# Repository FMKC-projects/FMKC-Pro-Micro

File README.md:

# FMKC Pro Micro
The FMKC Pro Micro is a fork of the Goldfish type-C pro micro Rev C. The reason why this is forked is that at the time of writing, type-C Pro Micros are either A) really expensive, or B) ugly looking. This fork is planned to be a community-themes pro micro and hence also openly shared. We'll try to include everything so that you could make your own PCBWay (or similar) or order.

## Risks
At the time of writing, we haven't yet done a order of this fork. Despite when this run has been done and the files are "ready", you are still using this at your own risk.

## Repo Contents
**/cad** - KiCad source files.  
**/doc** - Schematics
**/bom** - The BOM-file as .xslx (or some other format)

## License Information
Released under the Creative Commons Attribution Share-Alike 4.0 License.  
https://creativecommons.org/licenses/by-sa/4.0/  

Original Arduino Mini Design by Team Arduino.  
Arduino Pro Mini Design by Spark Fun Electronics.  
Pro Micro Design by Spark Fun Electronics.  
Goldfish Design by Dr Derivative.  

## Related Projects
* [Alvaro](https://github.com/Ariamelon/Alvaro) by Ariamelon - A modified goldfish using 0603 components instead of 0402
* [Comet](https://github.com/vattern/comet) by Tokas - A modified goldfish using a different USB-C connector
* [Goldfish-clone-JLCPCB](https://github.com/JeremyJStarcher/Goldfish-clone-JLCPCB) by Jeremy J Starcher - A modified goldfish designed to meet JLCPCB's assembly requirements
* Elite-C from keeb.io - An unrelated and closed source project with similar design goals

## Potential vendors
* Potential single units available after production by [olli.works](https://olli.works)

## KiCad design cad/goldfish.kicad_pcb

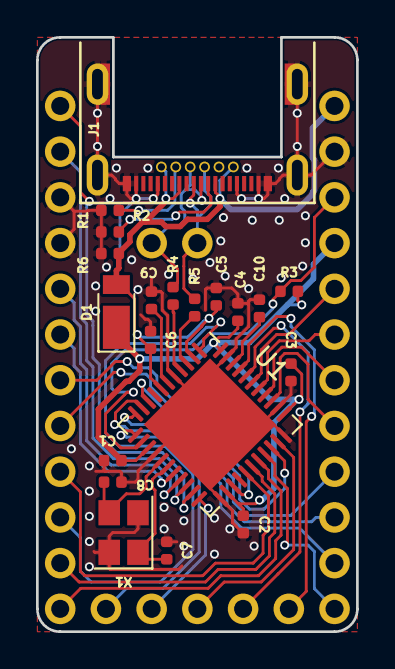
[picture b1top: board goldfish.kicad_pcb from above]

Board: 2 copper layers, 17.8 x 33.0 mm, 24 parts (0 on the bottom side), 37 nets.

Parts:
C1, C2, C3, C4, C5, C10: 0u1; C_0402_1005Metric
C6: 4u7; C_0402_1005Metric
C7, C8: 22p; C_0402_1005Metric
C9: 1u; C_0402_1005Metric
D1: D_Schottky; D_PowerDI-123
J1: USB-C; CX70M-24P1
J2: 01x02; Pins2
J3, J4: 01x12; Pins12
J5: 01x05; Pins5
R1, R2: 5k1; R_0402_1005Metric
R3, R6: 10k; R_0402_1005Metric
R4, R5: 22; R_0402_1005Metric
U1: ATmega32U4; QFN-44-1EP_7x7mm_P0.5mm_EP5.2x5.2mm_FORK
X1: 16MHz; Crystal_SMD_SeikoEpson_FA238-4Pin_3.2x2.5mm

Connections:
/D+: J1.A6, J1.B6, J2.1, R4.2
/D-: J1.A7, J1.B7, J2.2, R5.2
/PB1: J3.9, U1.9
/PB2: J3.11, U1.10
/PB3: J3.10, U1.11
/PB4: J4.2, U1.28
/PB5: J4.1, U1.29
/PB6: J3.12, U1.30
/PB7: J5.5, U1.12
/PC6: J4.5, U1.31
/PC7: J5.3, U1.32
/PD0: J4.7, U1.18
/PD1: J4.8, U1.19
/PD2: J4.11, U1.20
/PD3: J4.12, U1.21
/PD4: J4.6, U1.25
/PD5: J5.4, U1.22
/PD7: J4.4, U1.27
/PE6: J4.3, U1.1
/PF0: J5.1, U1.41
/PF1: J5.2, U1.40
/PF4: J3.5, U1.39
/PF5: J3.6, U1.38
/PF6: J3.7, U1.37
/PF7: J3.8, U1.36
/RESET: J3.3, R3.1, U1.13
GND: C1.2, C2.2, C3.2, C4.2, C5.2, C6.2, C7.2, C8.2, C9.2, C10.2, J1.A1, J1.A12, J1.B1, J1.B12, J1.S1, J3.2, J4.9, J4.10, R1.1, R2.1, R6.1, U1.5, U1.15, U1.23, U1.33, U1.35, U1.43, U1.45, X1.2, X1.4
unnamed: C7.1, U1.17, X1.1
unnamed: C8.1, U1.16, X1.3
unnamed: C9.1, U1.6
unnamed: C10.1, U1.42
unnamed: J1.A5, R1.2
unnamed: J1.B5, R2.2
unnamed: R4.1, U1.4
unnamed: R5.1, U1.3
VBUS: C5.1, C6.1, D1.2, J1.A4, J1.A9, J1.B4, J1.B9, J3.1, R6.2, U1.2, U1.7
VCC: C1.1, C2.1, C3.1, C4.1, D1.1, J3.4, R3.2, U1.14, U1.24, U1.34, U1.44

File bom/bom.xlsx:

Item # | *Ref Des | *Qty | Manufacturer | *Mfg Part # | Description / Value | *Package | Type | Your Instructions / Notes
 | R5,R4 | 2.0 | RALEC | RTT0222R0FTH | 1/16W ±1% ±100ppm/℃ 22Ω 0402 Chip Resistor - Surface Mount ROHS | 0402 | SMD | https://lcsc.com/product-detail/Chip-Resistor-Surface-Mount_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
 | C9 | 1.0 | FH(Guangdong Fenghua Advanced Tech) | 0402X105M6R3NT | X5R 6.3V ±20% 1uF 0402 Multilayer Ceramic Capacitors MLCC - SMD/SMT ROHS | 0402 | SMD | https://lcsc.com/product-detail/Multilayer-Ceramic-Capacitor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
 | C1,C2,C3,C4,C5,C10 | 6.0 | FH(Guangdong Fenghua Advanced Tech) | 0402B104K500NT | X7R 100nF ±10% 50V 0402 Multilayer Ceramic Capacitors MLCC - SMD/SMT ROHS | 0402 | SMD | https://lcsc.com/product-detail/Multilayer-Ceramic-Capacitor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
 | R3,R6 | 2.0 | RALEC | RTT021002FTH | 1/16W ±1% ±100ppm/℃ 10kΩ 0402 Chip Resistor - Surface Mount ROHS | 0402 | SMD | https://lcsc.com/product-detail/Chip-Resistor-Surface-Mount_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
 | C6 | 1.0 | FH(Guangdong Fenghua Advanced Tech) | 0402X475K100NT | X5R ±10% 10V 4.7uF 0402 Multilayer Ceramic Capacitors MLCC - SMD/SMT ROHS | 0402 | SMD | https://lcsc.com/product-detail/Multilayer-Ceramic-Capacitor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
 | U1 | 1.0 | Microchip Tech | ATMEGA32U4-MU | 2.7V ~ 5.5V 8-Bit AVR 16MHz FLASH QFN-44_7x7x05P ATMEL & AVR ROHS | QFN-44_7x7x05P | SMD | https://lcsc.com/product-detail/ATMEL-AVR_Microchip-Tech-ATM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
 | X1 | 1.0 | Seiko Epson | Q22FA2380186800 | SMD3225-4P Crystals ROHS | SMD3225-4P | SMD | https://lcsc.com/product-detail/Crystals_Seiko-Epson-Q22FA23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
 | C7,C8 | 2.0 | FH(Guangdong Fenghua Advanced Tech) | 0402CG220F500NT | C0G ±1% 50V 22pF 0402 Multilayer Ceramic Capacitors MLCC - SMD/SMT ROHS | 0402 | SMD | https://lcsc.com/product-detail/Multilayer-Ceramic-Capacitor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
 | R1,R2 | 2.0 | RALEC | RTT025101FTH | ±1% 1/16W ±100ppm/℃ 5.1kΩ 0402 Chip Resistor - Surface Mount ROHS | '0402 | SMD | https://lcsc.com/product-detail/Chip-Resistor-Surface-Mount_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
 | J1 | 1.0 | HRS(Hirose) | CX70M-24P1 | USB Connectors ROHS |  | SMD | https://lcsc.com/product-detail/USB-Connectors_HRS-Hirose-CX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
 | D1 | 1.0 | Diodes Incorporated | DFLS260Q-7 | PowerDI123 Schottky Barrier Diodes (SBD) ROHS | PowerDI123 | SMD | https://lcsc.com/product-detail/span-style-background-color-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

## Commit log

2021-08-25 Updated README, added preliminary BOM
2021-08-25 removed goldfish silk
2021-08-29 Making letters small
2021-08-29 update gitignore for plots
2021-09-01 adding silks
2021-09-03 tyty-c addition test
2021-09-03 update gitignore
2021-09-18 idk plotted things, pcb artworks etc random work, should prolly gitignore plot-folder but cba :D
